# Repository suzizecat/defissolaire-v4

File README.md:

# All-in-one (AIO) board for the "Défis solaires" contest of 2024.
Board files in `main/` folder.

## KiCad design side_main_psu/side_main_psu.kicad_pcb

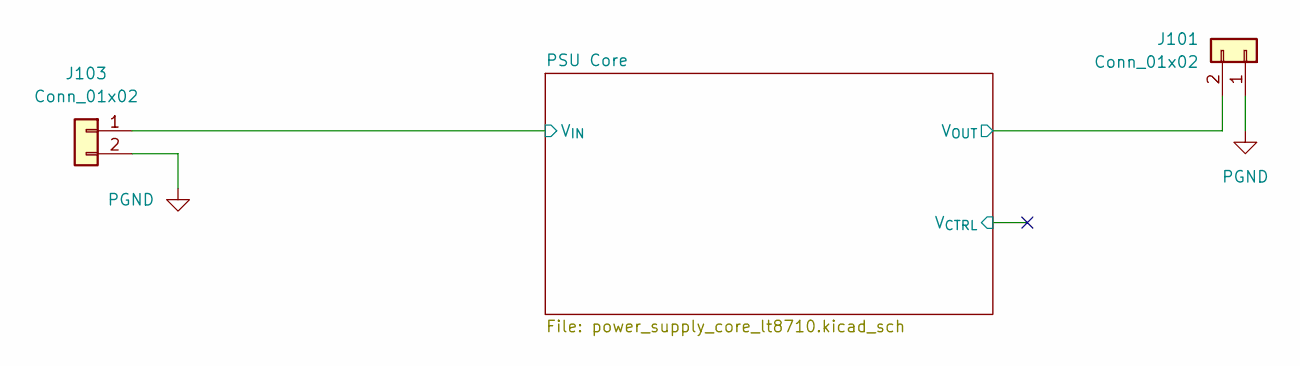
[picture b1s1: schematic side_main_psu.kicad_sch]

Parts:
J101, J103: Conn_01x02; TerminalBlock_WAGO_236-402_1x02_P5.00mm_45Degree

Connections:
/PSU Core/V_{IN}: J103.1; also elsewhere on the board
/PSU Core/V_{OUT}: J101.2; also elsewhere on the board
PGND: J101.1, J103.2; also elsewhere on the board

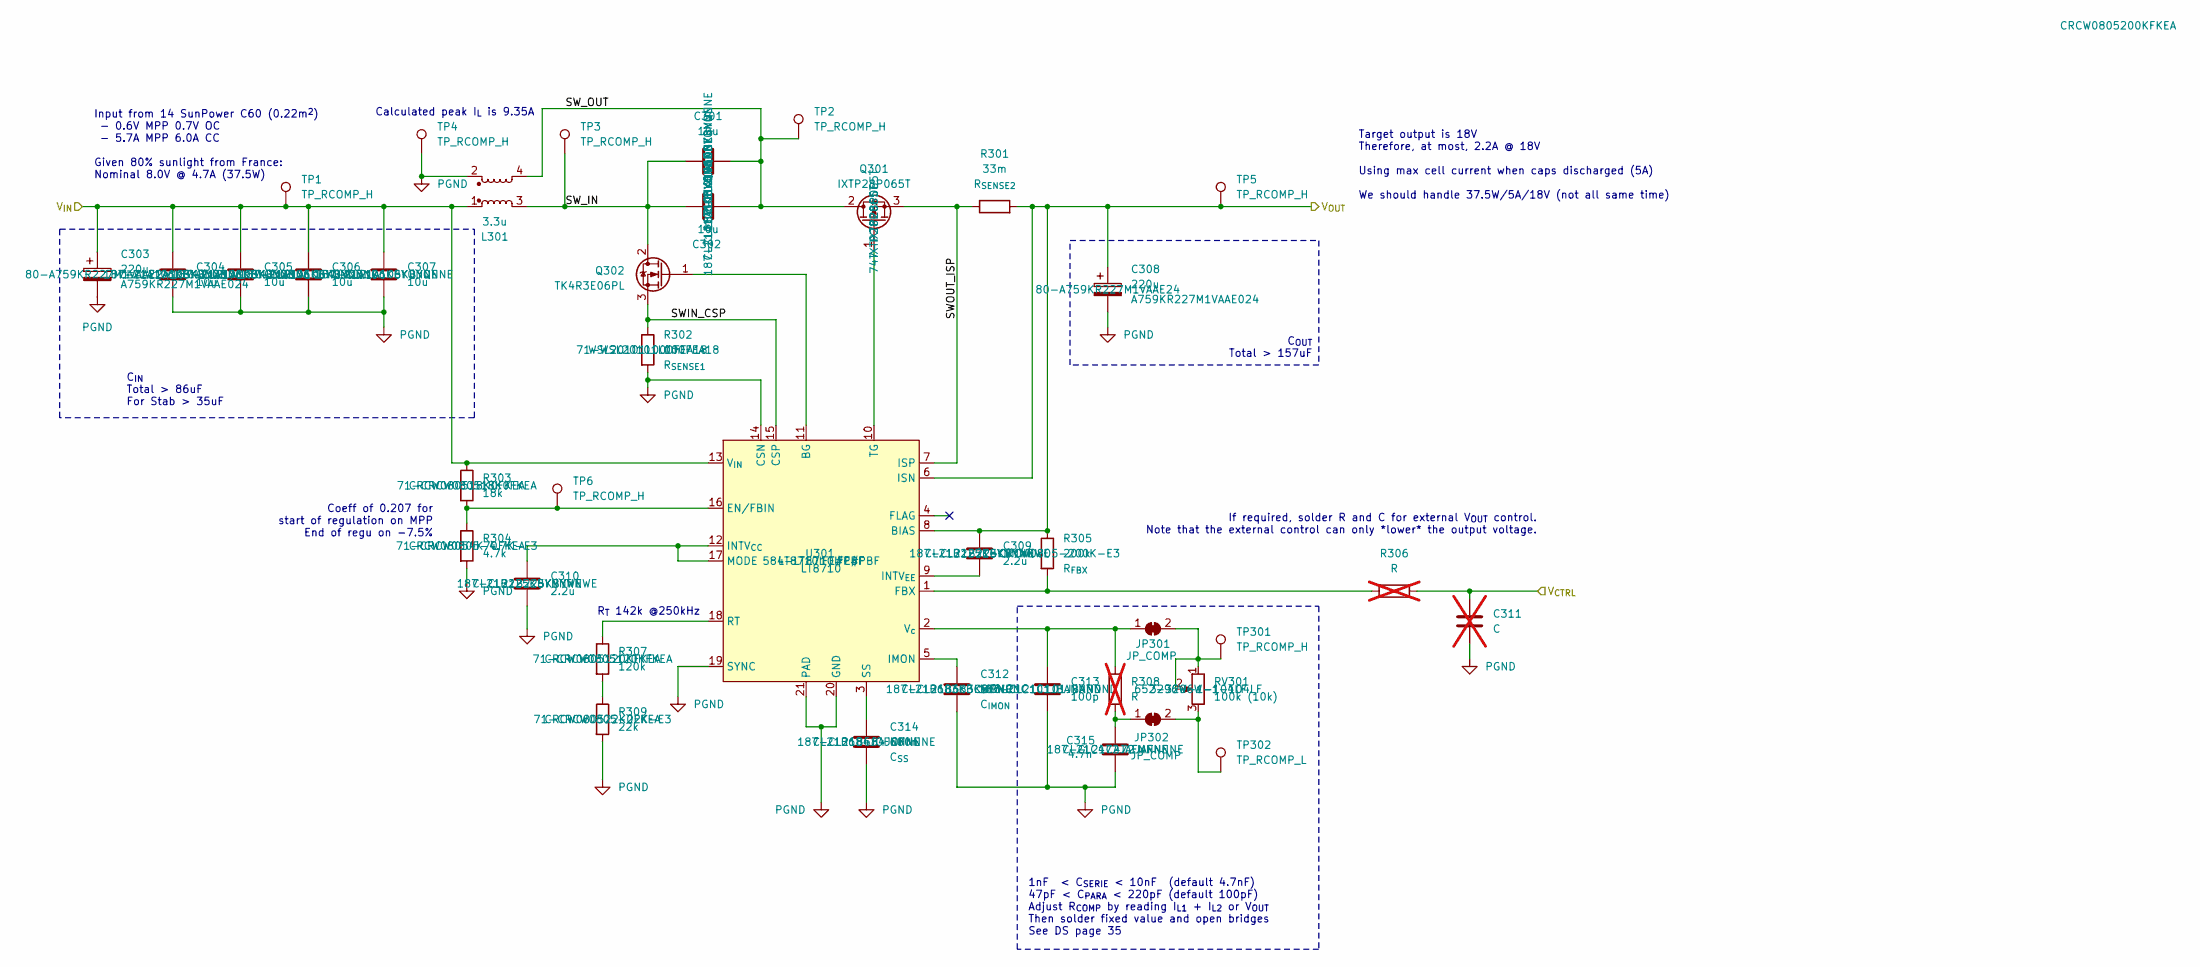
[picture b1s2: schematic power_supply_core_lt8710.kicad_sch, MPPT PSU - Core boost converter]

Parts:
C301, C302, C304, C305, C306, C307: 10u; C_0805_2012Metric; MPN CL21A106KBYQNNE; Mouser SKU 187-CL21A106KBYQNNE
C303, C308: 220u; CP_Radial_D8.0mm_P3.50mm; MPN A759KR227M1VAAE024; Mouser SKU 80-A759KR227M1VAAE24
C309, C310: 2.2u; C_0805_2012Metric; MPN CL21B225KBYNNWE; Mouser SKU 187-CL21B225KBYNNWE
C311: C; C_0805_2012Metric; not fitted
C312: 68n; C_0805_2012Metric; MPN CL21B683KBCWPNC; Mouser SKU 187-CL21B683KBCWPNC
C313: 100p; C_0805_2012Metric; MPN CL21C101JBANNND; Mouser SKU 187-CL21C101JBANNND
C314: 680n; C_0805_2012Metric; MPN CL21B684JOFNNNE; Mouser SKU 187-CL21B684JOFNNNE
C315: 4.7n; C_0805_2012Metric; MPN CL21C472JAFNNNE; Mouser SKU 187-CL21C472JAFNNNE
JP301, JP302: JP_COMP; SolderJumper-2_P1.3mm_Open_TrianglePad1.0x1.5mm
L301: 3.3u; Coilcraft_MSD1514
Q301: IXTP28P065T; TO-220-3_Horizontal_TabUp; MPN IXTP28P065T; Mouser SKU 747-IXTP28P065T
Q302: TK4R3E06PL; TO-220-3_Horizontal_TabUp; MPN TK4R3E06PL; Mouser SKU 757-TK4R3E06PLS1X
R301: 33m; R_2010_5025Metric
R302: 1m; R_2010_5025Metric; MPN WSL20101L000FEA18; Mouser SKU 71-WSL20101L000FEA18
R303: 18k; R_0805_2012Metric; MPN CRCW080518K0FKEA; Mouser SKU 71-CRCW080518K0FKEA
R304: 4.7k; R_0805_2012Metric; MPN CRCW08054K70FKEA; Mouser SKU 71-CRCW0805-4.7K-E3
R305: 200k; R_0805_2012Metric; MPN CRCW0805200KFKEA; Mouser SKU 71-CRCW0805-200K-E3
R306, R308: R; R_0805_2012Metric; not fitted
R307: 120k; R_0805_2012Metric; MPN CRCW0805120KFKEA; Mouser SKU 71-CRCW0805120KFKEA
R309: 22k; R_0805_2012Metric; MPN CRCW080522K0FKEA; Mouser SKU 71-CRCW0805-22K-E3
RV301: 100k (10k); Potentiometer_Bourns_3296W_Vertical; MPN 3296W-1-104LF; Mouser SKU 652-3296W-1-104LF
TP1, TP2, TP3, TP4, TP5, TP6, TP301: TP_RCOMP_H; TestPoint_Keystone_5010-5014_Multipurpose
TP302: TP_RCOMP_L; TestPoint_Keystone_5010-5014_Multipurpose
U301: LT8710; HTSSOP-20-1EP_4.4x6.5mm_P0.65mm_EP2.74x3.86mm; MPN LT8710IFE#PBF; Mouser SKU 584-LT8710IFE#PBF

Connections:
/PSU Core/SWIN_CSP: Q302.3 (S), R302.1, U301.15 (CSP)
/PSU Core/SWOUT_ISP: Q301.3 (S), R301.1, U301.7 (ISP)
/PSU Core/SW_IN: C301.2, C302.2, L301.3, Q302.2 (D), TP3.1
/PSU Core/SW_OUT: C301.1, C302.1, L301.4, Q301.2 (D), TP2.1
/PSU Core/V_{CTRL}: C311.1, R306.2
/PSU Core/V_{IN}: C303.1, C304.1, C305.1, C306.1, C307.1, L301.1, R303.1, TP1.1, U301.13 (V_{IN}); also elsewhere on the board
/PSU Core/V_{OUT}: C308.1, C309.1, R301.2, R305.1, TP5.1, U301.6 (ISN), U301.8 (BIAS); also elsewhere on the board
unnamed: C313.1, JP301.1 (A), R308.1, U301.2 (V_{c})
unnamed: JP301.2 (B), RV301.1, RV301.2, TP301.1
unnamed: C315.1, JP302.1 (A), R308.2
unnamed: JP302.2 (B), RV301.3, TP302.1
unnamed: Q301.1 (G), U301.10 (TG)
unnamed: Q302.1 (G), U301.11 (BG)
unnamed: R307.2, R309.1
unnamed: R303.2, R304.1, TP6.1, U301.16 (EN/FBIN)
unnamed: R305.2, R306.1, U301.1 (FBX)
unnamed: C312.1, U301.5 (IMON)
unnamed: C310.1, U301.12 (INTV_{CC}), U301.17 (MODE)
unnamed: C309.2, U301.9 (INTV_{EE})
unnamed: R307.1, U301.18 (RT)
unnamed: C314.1, U301.3 (SS)
PGND: C303.2, C304.2, C305.2, C306.2, C307.2, C308.2, C310.2, C311.2, C312.2, C313.2, C314.2, C315.2, L301.2, R302.2, R304.2, R309.2, TP4.1, U301.14 (CSN), U301.19 (SYNC), U301.20 (GND), U301.21 (PAD); also elsewhere on the board

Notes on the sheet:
If required, solder R and C for external V_{OUT} control. Note that the external control can only *lower* the output voltage.
1nF < C_{SERIE} < 10nF (default 4.7nF) 47pF < C_{PARA} < 220pF (default 100pF) Adjust R_{COMP} by reading I_{L1} + I_{L2} or V_{OUT} Then solder fixed value and open bridges See DS page 35
C_{IN} Total > 86uF For Stab > 35uF
R_{T} 142k @250kHz
Input from 14 SunPower C60 (0.22m^{2}) - 0.6V MPP 0.7V OC - 5.7A MPP 6.0A CC Given 80% sunlight from France: Nominal 8.0V @ 4.7A (37.5W)
Calculated peak I_{L} is 9.35A
C_{OUT} Total > 157uF
Coeff of 0.207 for start of regulation on MPP End of regu on -7.5%
Target output is 18V Therefore, at most, 2.2A @ 18V Using max cell current when caps discharged (5A) We should handle 37.5W/5A/18V (not all same time)

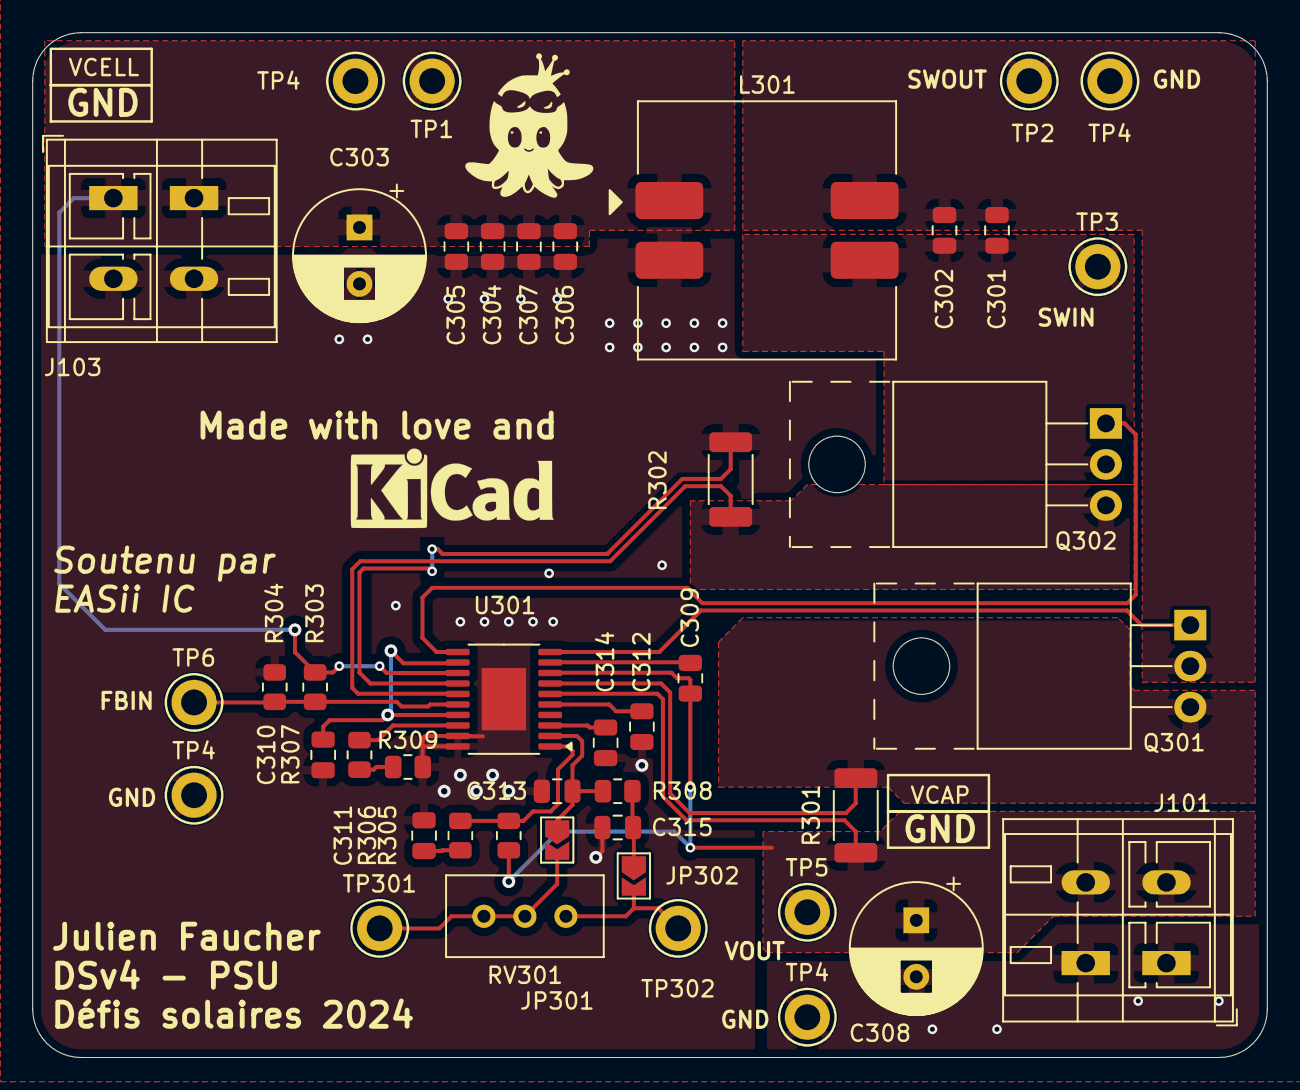
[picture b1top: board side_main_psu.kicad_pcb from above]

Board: 2 copper layers, 76.5 x 63.5 mm, 44 parts (0 on the bottom side), 22 nets.

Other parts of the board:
TP4#2, TP4#3, TP4#4: TP_GND; TestPoint_Keystone_5010-5014_Multipurpose

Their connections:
PGND: TP4#2.1, TP4#3.1, TP4#4.1; also elsewhere on the board

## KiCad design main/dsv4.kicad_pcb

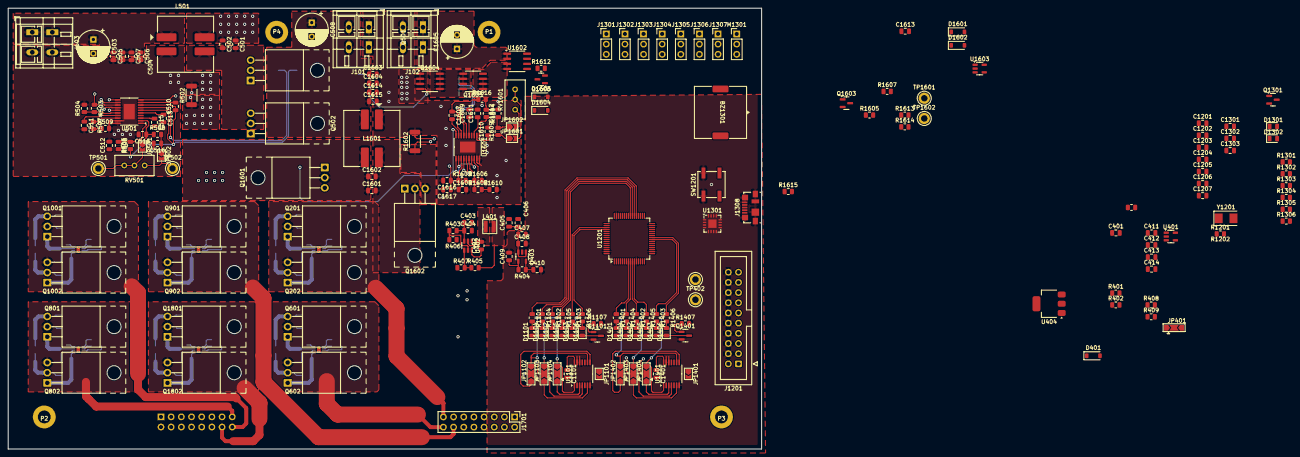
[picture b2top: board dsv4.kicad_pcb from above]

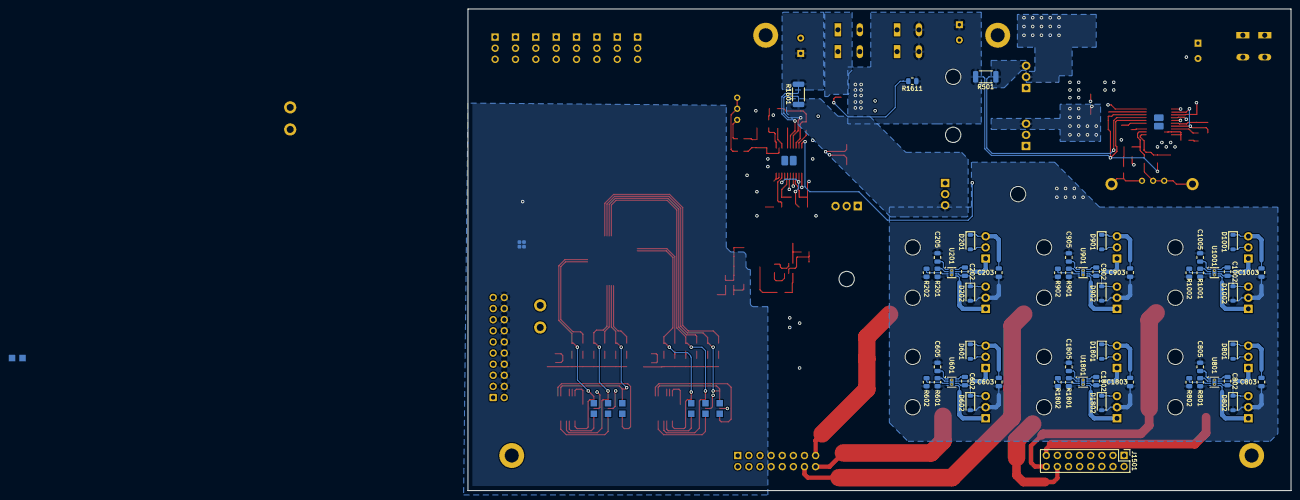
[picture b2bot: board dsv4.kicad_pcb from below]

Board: 4 copper layers, 188.0 x 110.0 mm, 261 parts (52 on the bottom side), 170 nets.

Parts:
BZ1301: PKLCS1212E4001-R1
C202, C402, C404, C408, C413, C602, C802, C902, C1002, C1101, C1201, C1202, C1203, C1204, C1205, C1303, C1401, C1617, C1802: 100n; C_0805_2012Metric
C203, C603, C803, C903, C1003, C1803: 1n; C_0805_2012Metric
C205, C407, C410, C411, C412, C414, C605, C805, C905, C1005, C1805: 1u; C_0805_2012Metric
C401, C1613: 4.7u; C_0805_2012Metric
C403, C510, C511, C1607, C1608: 2.2u; C_0805_2012Metric
C405, C406, C501, C502, C504, C505, C506, C507, C1601, C1602, C1603, C1604, C1614, C1615, C1616: 10u; C_0805_2012Metric
C409: 10n; C_0805_2012Metric
C503, C508, C1605: 220u; CP_Radial_D8.0mm_P3.50mm
C512: C; C_0805_2012Metric
C513, C1609: 62n; C_0805_2012Metric
C514, C1610: 100p; C_0805_2012Metric
C515, C1611: 560n; C_0805_2012Metric
C516, C1612: 4.7n; C_0805_2012Metric
C1206, C1207: 18p; C_0805_2012Metric
C1301, C1302: 47p; C_0805_2012Metric
D201, D202, D601, D602, D801, D802, D901, D902, D1001, D1002, D1601, D1602, D1603, D1604, D1801, D1802: B5819W-TP; D_SOD-123
D401: XBS104S14R-G; D_SOD-123
D1101, D1102, D1103, D1401, D1402, D1403: RED; LED_0805_2012Metric
D1104, D1105, D1106, D1404, D1405, D1406: BLUE; LED_0805_2012Metric
D1301, D1302: LED; LED_0805_2012Metric
J101, J102, J103: Conn_01x02; TerminalBlock_WAGO_236-402_1x02_P5.00mm_45Degree
J1201: Conn_ARM_JTAG_SWD_20; IDC-Header_2x10_P2.54mm_Vertical
J1301: Transponder; PinHeader_1x03_P2.54mm_Vertical
J1302, J1303, J1304, J1305, J1306, J1307: Conn_01x03; PinHeader_1x03_P2.54mm_Vertical
J1308: USB_B_Micro; USB_Micro-B_Molex_47346-0001
J1501, J1701: Conn_02x08_Odd_Even; PinHeader_2x08_P2.54mm_Vertical
JP401: DRIVE VSEL; SolderJumper-3_P2.0mm_Open_TrianglePad1.0x1.5mm
JP501, JP502, JP1601, JP1602: JP_COMP; SolderJumper-2_P1.3mm_Open_TrianglePad1.0x1.5mm
JP1101, JP1401: AND_PWR; SolderJumper-2_P1.3mm_Open_TrianglePad1.0x1.5mm
JP1102, JP1103, JP1104, JP1402, JP1403, JP1404: AND_BYP; SolderJumper-3_P2.0mm_Open_TrianglePad1.0x1.5mm
L401: 3.3u; VLS3015CX
L501, L1601: 3.3u; Coilcraft_MSD1260T
M1301: Servo direction; PinHeader_1x03_P2.54mm_Vertical
P1, P2, P3, P4: CONN_01X01; MountingHole_3.2mm_M3_ISO7380_Pad
Q201, Q202, Q502, Q601, Q602, Q801, Q802, Q901, Q902, Q1001, Q1002, Q1602, Q1801, Q1802: TK4R3E06PL; TO-220-3_Horizontal_TabUp
Q501, Q1601: IXTP28P065T; TO-220-3_Horizontal_TabUp
Q1101, Q1301, Q1401, Q1603, Q1606: IRLML0030; SOT-23
Q1604, Q1605: FDS6681Z; SOIC-8_3.9x4.9mm_P1.27mm
R201, R202, R601, R602, R801, R802, R901, R902, R1001, R1002, R1107, R1302, R1407, R1801, R1802: 100k; R_0805_2012Metric
R401, R406, R1613: 33k; R_0805_2012Metric
R402, R1614: 5.6k; R_0805_2012Metric
R403, R405: 150k; R_0805_2012Metric
R404: NM; R_0805_2012Metric
R407, R409: 20k; R_0805_2012Metric
R408: 2k; R_0805_2012Metric
R501, R1601: 33m; R_2010_5025Metric
R502, R1602: 1m; R_2010_5025Metric
R503, R1603: 18k; R_0805_2012Metric
R504, R1605, R1606: 4.7k; R_0805_2012Metric
R505: 200k; R_0805_2012Metric
R506, R508, R1609: R; R_0805_2012Metric
R507, R1608: 120k; R_0805_2012Metric
R509, R1610: 22k; R_0805_2012Metric
R1101, R1102, R1103, R1104, R1105, R1106, R1401, R1402, R1403, R1404, R1405, R1406: 3k3; R_0805_2012Metric
R1201, R1202, R1607, R1611, R1612, R1615: 10k; R_0805_2012Metric
R1301, R1305, R1306: 1k; R_0805_2012Metric
R1303, R1304: 27; R_0805_2012Metric
R1604, R1616: 68k; R_0805_2012Metric
RV501, RV1601: 100k (10k); Potentiometer_Bourns_3296W_Vertical
SW1201: B3SL-1022P; SW_SPST_B3SL-1022P
TP401, TP402: TestPoint; TestPoint_Keystone_5010-5014_Multipurpose
TP501, TP1601: TP_RCOMP_H; TestPoint_Keystone_5010-5014_Multipurpose
TP502, TP1602: TP_RCOMP_L; TestPoint_Keystone_5010-5014_Multipurpose
U201, U601, U801, U901, U1001, U1801: LM2105; WSON-8-1EP_2x2mm_P0.5mm_EP0.9x1.6mm_ThermalVias
U401, U1603: TSV911xxLx; SOT-23-5
U402: LMR51430; SOT-23-6
U403: LDK130M33R; SOT-23-5
U404: LM317_SOT-223; SOT-223-3_TabPin2
U501, U1601: LT8710; HTSSOP-20-1EP_4.4x6.5mm_P0.65mm_EP2.74x3.86mm
U1101, U1401: 74LS08; TSSOP-14_4.4x5mm_P0.65mm
U1201: STM32L476RGTx; LQFP-64_10x10mm_P0.5mm
U1301: FT230XQ; QFN-16-1EP_4x4mm_P0.65mm_EP2.1x2.1mm
U1602: TMCS1101; SOIC-8_3.9x4.9mm_P1.27mm
Y1201: 8MHz; Crystal_SMD_5032-2Pin_5.0x3.2mm

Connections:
+3.3V: C410.1, C1201.1, C1202.1, C1203.1, C1204.1, J1201.2 (VCC/NC), J1501.1, J1701.1, JP1101.2 (B), JP1401.2 (B), R404.1, R1201.1, R1615.1, TP401.1, U401.5 (V+), U403.5 (OUT), U1201.13 (VDDA), U1201.19 (VDD), U1201.32 (VDD), U1201.64 (VDD), U1602.8 (VS), U1603.5 (V+)
+5V: C405.1, C406.1, C407.1, C408.1, J1301.2, J1302.2, J1303.2, J1304.2, J1305.2, J1306.2, J1307.2, L401.2, M1301.2 (+), R405.2, TP402.1, U403.1 (IN), U403.3 (EN)
/CODA.A: J1701.2, U1201.14 (PA0)
/CODA.B: J1701.3, U1201.15 (PA1)
/CODB.A: J1501.2, U1201.22 (TIM3_CH1)
/CODB.B: J1501.3, U1201.23 (TIM3_CH2)
/CSN_1: J1701.11, U1201.3 (PC14)
/CSN_2: J1501.11, U1201.4 (PC15)
/MCU/BAT_OK: R1615.2, U1201.29 (PB10), U1601.4 (FLAG)
/MCU/BAT_USE: D1602.2 (A), Q1606.1 (G), U1201.30 (PB11)
/MCU/EN_BIP: Q1301.1 (G), R1302.1, U1201.50 (PA15)
/MCU/MEAS_IBAT: U1201.21 (ADC1_IN10), U1602.7 (VOUT)
/MCU/MEAS_VBAT: U1201.20 (ADC1_IN9), U1603.1, U1603.4 (-)
/MCU/MEAS_VCAP: U401.1, U401.4 (-), U1201.26 (ADC1_IN15)
/MCU/MOT1.AH: R901.1, R1401.1, U901.2 (INH), U1201.8 (PC0)
/MCU/MOT1.AL: JP1402.2 (C), R902.1, U901.3 (INL)
/MCU/MOT1.BH: R201.1, R1402.1, U201.2 (INH), U1201.10 (PC2)
/MCU/MOT1.BL: JP1403.2 (C), R202.1, U201.3 (INL)
/MCU/MOT1.CH: R601.1, R1403.1, U601.2 (INH), U1201.24 (PC4)
/MCU/MOT1.CL: JP1404.2 (C), R602.1, U601.3 (INL)
/MCU/MOT1_CMD.AL: JP1402.3 (B), R1404.1, U1201.9 (PC1), U1401.9
/MCU/MOT1_CMD.BL: JP1403.3 (B), R1405.1, U1201.11 (PC3), U1401.4
/MCU/MOT1_CMD.CL: JP1404.3 (B), R1406.1, U1201.25 (PC5), U1401.1
/MCU/MOT1_PWM: U1201.35 (TIM15_CH1), U1401.2, U1401.5, U1401.10
/MCU/MOT2.AH: R1101.1, R1801.1, U1201.37 (PC6), U1801.2 (INH)
/MCU/MOT2.AL: JP1102.2 (C), R1802.1, U1801.3 (INL)
/MCU/MOT2.BH: R801.1, R1102.1, U801.2 (INH), U1201.39 (PC8)
/MCU/MOT2.BL: JP1103.2 (C), R802.1, U801.3 (INL)
/MCU/MOT2.CH: R1001.1, R1103.1, U1001.2 (INH), U1201.51 (PC10)
/MCU/MOT2.CL: JP1104.2 (C), R1002.1, U1001.3 (INL)
/MCU/MOT2_CMD.AL: JP1102.3 (B), R1104.1, U1101.9, U1201.38 (PC7)
/MCU/MOT2_CMD.BL: JP1103.3 (B), R1105.1, U1101.4, U1201.40 (PC9)
/MCU/MOT2_CMD.CL: JP1104.3 (B), R1106.1, U1101.1, U1201.52 (PC11)
/MCU/MOT2_PWM: U1101.2, U1101.5, U1101.10, U1201.36 (TIM15_CH2)
/MCU/MOT_LED_EN: Q1101.1 (G), Q1401.1 (G), R1107.1, R1407.1, U1201.34 (PB13)
/MCU/NRST: C1205.1, J1201.3 (~TRST), R1201.2, SW1201.2, U1201.7 (NRST)
/MCU/OSC_1: C1206.1, U1201.5 (RCC_OSC_IN), Y1201.1
/MCU/OSC_2: C1207.1, U1201.6 (RCC_OSC_OUT), Y1201.2
/MCU/RADIO1: J1302.1, U1201.41 (PA8)
/MCU/RADIO2: J1303.1, U1201.42 (PA9)
/MCU/RADIO3: J1304.1, M1301.1 (PWM), U1201.43 (PA10)
/MCU/RADIO4: J1305.1, U1201.44 (PA11)
/MCU/RADIO5: J1306.1, U1201.58 (TIM4_CH1)
/MCU/RADIO6: J1307.1, U1201.59 (TIM4_CH2)
/MCU/SWCLK: J1201.9 (TCK/SWCLK), U1201.49 (SYS_JTCK-SWCLK)
/MCU/SWDIO: J1201.7 (TMS/SWDIO), U1201.46 (SYS_JTMS-SWDIO)
/MCU/USART.RX: U1201.17 (USART2_RX), U1301.15 (TXD)
/MCU/USART.TX: U1201.16 (USART2_TX), U1301.2 (RXD)
/MCU/~BAT_CHARGE: D1601.2 (A), U1201.33 (PB12)
/MOT A Connection/MOT.A: C902.2, D901.2 (A), D902.1 (K), J1701.14, Q901.2 (D), Q902.3 (S), U901.6 (SH)
/MOT A Connection/MOT.B: C202.2, D201.2 (A), D202.1 (K), J1701.15, Q201.2 (D), Q202.3 (S), U201.6 (SH)
/MOT A Connection/MOT.C: C602.2, D601.2 (A), D602.1 (K), J1701.16, Q601.2 (D), Q602.3 (S), U601.6 (SH)
/MOT B Connection/MOT.A: C1802.2, D1801.2 (A), D1802.1 (K), J1501.14, Q1801.2 (D), Q1802.3 (S), U1801.6 (SH)
/MOT B Connection/MOT.B: C802.2, D801.2 (A), D802.1 (K), J1501.15, Q801.2 (D), Q802.3 (S), U801.6 (SH)
/MOT B Connection/MOT.C: C1002.2, D1001.2 (A), D1002.1 (K), J1501.16, Q1001.2 (D), Q1002.3 (S), U1001.6 (SH)
/PSU/5VSW: C402.2, L401.1, U402.2 (SW)
/PSU/Battery chagrer/BATT_RET_PATH: Q1605.1 (S), Q1605.2 (S), Q1605.3 (S), R1612.1, U1602.3 (OUT), U1602.4 (OUT)
/PSU/Battery chagrer/BAT_RET_MID: Q1604.5 (D), Q1604.6 (D), Q1604.7 (D), Q1604.8 (D), Q1605.5 (D), Q1605.6 (D), Q1605.7 (D), Q1605.8 (D)
/PSU/Battery chagrer/SWIN_CSP: Q1602.3 (S), R1602.1, U1601.15 (CSP)
/PSU/Battery chagrer/SWOUT_ISP: Q1601.3 (S), R1601.1, U1601.7 (ISP)
/PSU/Battery chagrer/SW_IN: C1601.2, C1602.2, L1601.4, Q1602.2 (D)
/PSU/Battery chagrer/SW_OUT: C1601.1, C1602.1, L1601.3, Q1601.2 (D)
/PSU/Input PSU/SWIN_CSP: Q502.3 (S), R502.1, U501.15 (CSP)
/PSU/Input PSU/SWOUT_ISP: Q501.3 (S), R501.1, U501.7 (ISP)
/PSU/Input PSU/SW_IN: C501.2, C502.2, L501.3, Q502.2 (D)
/PSU/Input PSU/SW_OUT: C501.1, C502.1, L501.4, Q501.2 (D)
/PSU/Input PSU/V_{CTRL}: C512.1, R506.2
/PSU/V_{CELL}: C503.1, C504.1, C505.1, C506.1, C507.1, J103.1, L501.1, R503.1, U501.13 (V_{IN})
/Radio and misc/V_{FTDI}: C1303.1, D1301.2 (A), D1302.2 (A), U1301.1 (VCCIO), U1301.8 (3V3OUT), U1301.9 (~RESET)
/SPI.CLK: J1501.10, J1701.10, U1201.55 (SPI1_SCK)
/SPI.MISO: J1501.8, J1701.8, U1201.56 (SPI1_MISO)
/SPI.MOSI: J1501.9, J1701.9, U1201.57 (SPI1_MOSI)
GNDD: C203.2, C205.2, C401.2, C403.2, C404.2, C405.2, C406.2, C407.2, C408.2, C409.2, C410.2, C411.2, C412.2, C413.2, C414.2, C503.2, C504.2, C505.2, C506.2, C507.2, C508.2, C511.2, C512.2, C513.2, C514.2, C515.2, C516.2, C603.2, C605.2, C803.2, C805.2, C903.2, C905.2, C1003.2, C1005.2, C1101.2, C1201.2, C1202.2, C1203.2, C1204.2, C1205.2, C1206.2, C1207.2, C1301.2, C1302.2, C1303.2, C1401.2, C1603.2, C1604.2, C1605.2, C1608.2, C1609.2, C1610.2, C1611.2, C1612.2, C1613.2, C1614.2, C1615.2, C1616.2, C1617.2, C1803.2, C1805.2, D202.2 (A), D602.2 (A), D802.2 (A), D902.2 (A), D1002.2 (A), D1802.2 (A), J101.1, J102.2, J103.2, J1201.4 (GND), J1201.6 (GND), J1201.8 (GND), J1201.10 (GND), J1201.12 (GND), J1201.14 (GND), J1201.16 (GND), J1201.18 (GND), J1201.20 (GND), J1301.3, J1302.3, J1303.3, J1304.3, J1305.3, J1306.3, J1307.3, J1308.5 (GND), J1308.6 (Shield), J1501.12, J1501.13, J1701.12, J1701.13, L501.2, L1601.1, M1301.3 (-), Q202.2 (D), Q602.2 (D), Q802.2 (D), Q902.2 (D), Q1002.2 (D), Q1101.2 (S), Q1301.2 (S), Q1401.2 (S), Q1603.2 (S), Q1606.2 (S), Q1802.2 (D), R201.2, R202.2, R402.2, R406.1, R407.1, R409.2, R502.2, R504.2, R509.2, R601.2, R602.2, R801.2, R802.2, R901.2, R902.2, R1001.2, R1002.2, R1107.2, R1202.1, R1302.2, R1407.2, R1602.2, R1606.2, R1607.2, R1610.2, R1614.2, R1801.2, R1802.2, SW1201.1, U201.4 (GND), U201.9 (GND), U401.2 (V-), U402.1 (GND), U403.2 (GND), U501.14 (CSN), U501.19 (SYNC), U501.20 (GND), U501.21 (PAD), U601.4 (GND), U601.9 (GND), U801.4 (GND), U801.9 (GND), U901.4 (GND), U901.9 (GND), U1001.4 (GND), U1001.9 (GND), U1101.7 (GND), U1101.12, U1101.13, U1201.12 (VSSA), U1201.18 (VSS), U1201.31 (VSS), U1201.47 (VSS), U1201.63 (VSS), U1301.3 (GND), U1301.13 (GND), U1301.17 (GND), U1401.7 (GND), U1401.12, U1401.13, U1601.14 (CSN), U1601.19 (SYNC), U1601.20 (GND), U1601.21 (PAD), U1602.5 (GND), U1602.6 (NC), U1603.2 (V-), U1801.4 (GND), U1801.9 (GND)
IN: C1605.1, C1607.1, J102.1, R1601.2, R1613.1, R1616.1, U1601.6 (ISN), U1601.8 (BIAS), U1602.1 (IN), U1602.2 (IN)
unnamed: BZ1301.2 (-), Q1301.3 (D), R1301.2
unnamed: C414.1, D401.2 (A), R408.2, R409.1, U404.1 (ADJ)
unnamed: C411.1, D401.1 (K), JP401.3 (B), R408.1, U404.2 (VO)
unnamed: D1101.2 (A), R1101.2
unnamed: D1101.1 (K), D1102.1 (K), D1103.1 (K), D1104.1 (K), D1105.1 (K), D1106.1 (K), Q1101.3 (D)
unnamed: D1102.2 (A), R1102.2
unnamed: D1103.2 (A), R1103.2
unnamed: D1104.2 (A), R1104.2
unnamed: D1105.2 (A), R1105.2
unnamed: D1106.2 (A), R1106.2
unnamed: D1301.1 (K), R1305.1
unnamed: D1302.1 (K), R1306.1
unnamed: D1401.2 (A), R1401.2
unnamed: D1401.1 (K), D1402.1 (K), D1403.1 (K), D1404.1 (K), D1405.1 (K), D1406.1 (K), Q1401.3 (D)
unnamed: D1402.2 (A), R1402.2
unnamed: D1403.2 (A), R1403.2
unnamed: D1404.2 (A), R1404.2
unnamed: D1405.2 (A), R1405.2
unnamed: D1406.2 (A), R1406.2
unnamed: D1601.1 (K), D1602.1 (K), R1605.1, R1607.1
unnamed: D1603.2 (A), Q1604.4 (G), R1611.2
unnamed: D1603.1 (K), D1604.1 (K), Q1606.3 (D)
unnamed: D1604.2 (A), Q1605.4 (G), R1612.2
unnamed: C1301.1, J1308.3 (D+), R1304.2
unnamed: C1302.1, J1308.2 (D-), R1303.2
unnamed: J1308.1 (VBUS), U1301.10 (VCC)
unnamed: C514.1, JP501.1 (A), R508.1, U501.2 (V_{c})
unnamed: JP501.2 (B), RV501.1, RV501.2, TP501.1
unnamed: C516.1, JP502.1 (A), R508.2
unnamed: JP502.2 (B), RV501.3, TP502.1
unnamed: C1101.1, JP1101.1 (A), U1101.14 (VCC)
unnamed: JP1102.1 (A), U1101.8
unnamed: JP1103.1 (A), U1101.6
unnamed: JP1104.1 (A), U1101.3
unnamed: C1401.1, JP1401.1 (A), U1401.14 (VCC)
unnamed: JP1402.1 (A), U1401.8
unnamed: JP1403.1 (A), U1401.6
unnamed: JP1404.1 (A), U1401.3
unnamed: C1610.1, JP1601.1 (A), R1609.1, U1601.2 (V_{c})
unnamed: JP1601.2 (B), RV1601.1, RV1601.2, TP1601.1
unnamed: C1612.1, JP1602.1 (A), R1609.2
unnamed: JP1602.2 (B), RV1601.3, TP1602.1
unnamed: Q201.1 (G), U201.7 (GH)
unnamed: Q202.1 (G), U201.5 (GL)
unnamed: Q501.1 (G), U501.10 (TG)
unnamed: Q502.1 (G), U501.11 (BG)
unnamed: Q601.1 (G), U601.7 (GH)
unnamed: Q602.1 (G), U601.5 (GL)
unnamed: Q801.1 (G), U801.7 (GH)
unnamed: Q802.1 (G), U801.5 (GL)
unnamed: Q901.1 (G), U901.7 (GH)
unnamed: Q902.1 (G), U901.5 (GL)
unnamed: Q1001.1 (G), U1001.7 (GH)
unnamed: Q1002.1 (G), U1001.5 (GL)
unnamed: Q1601.1 (G), U1601.10 (TG)
unnamed: Q1602.1 (G), U1601.11 (BG)
unnamed: Q1603.3 (D), R1603.2, R1606.1, U1601.16 (EN/FBIN)
unnamed: Q1603.1 (G), R1605.2
unnamed: Q1801.1 (G), U1801.7 (GH)
unnamed: Q1802.1 (G), U1801.5 (GL)
unnamed: R507.2, R509.1
unnamed: R1604.1, R1616.2
unnamed: R1608.2, R1610.1
unnamed: C202.1, U201.8 (BST)
unnamed: C401.1, R401.2, R402.1, U401.3 (+)
unnamed: C402.1, U402.6 (BOOT)
unnamed: R403.1, R406.2, U402.5 (EN)
unnamed: R405.1, R407.2, U402.4 (FB)
unnamed: C409.1, R404.2, U403.4 (BP)
unnamed: R503.2, R504.1, U501.16 (EN/FBIN)
unnamed: R505.2, R506.1, U501.1 (FBX)
unnamed: C513.1, U501.5 (IMON)
unnamed: C511.1, U501.12 (INTV_{CC}), U501.17 (MODE)
unnamed: C510.2, U501.9 (INTV_{EE})
unnamed: R507.1, U501.18 (RT)
unnamed: C515.1, U501.3 (SS)
unnamed: C602.1, U601.8 (BST)
unnamed: C802.1, U801.8 (BST)
unnamed: C902.1, U901.8 (BST)
unnamed: C1002.1, U1001.8 (BST)
unnamed: R1202.2, U1201.60 (BOOT0)
unnamed: R1305.2, U1301.11 (CBUS1)
unnamed: R1306.2, U1301.5 (CBUS2)
unnamed: R1303.1, U1301.7 (USBDM)
unnamed: R1304.1, U1301.6 (USBDP)
unnamed: R1604.2, U1601.1 (FBX)
unnamed: C1609.1, U1601.5 (IMON)
unnamed: C1608.1, U1601.12 (INTV_{CC}), U1601.17 (MODE)
unnamed: C1607.2, U1601.9 (INTV_{EE})
unnamed: R1608.1, U1601.18 (RT)
unnamed: C1611.1, U1601.3 (SS)
unnamed: C1613.1, R1613.2, R1614.1, U1603.3 (+)
unnamed: C1802.1, U1801.8 (BST)
PGND: P1.1, P2.1, P3.1, P4.1
VCAP: C203.1, C403.1, C404.1, C412.1, C413.1, C508.1, C510.1, C603.1, C803.1, C903.1, C1003.1, C1603.1, C1604.1, C1614.1, C1615.1, C1616.1, C1617.1, C1803.1, D201.1 (K), D601.1 (K), D801.1 (K), D901.1 (K), D1001.1 (K), D1801.1 (K), J101.2, JP401.1 (A), L1601.2, Q201.3 (S), Q601.3 (S), Q801.3 (S), Q901.3 (S), Q1001.3 (S), Q1604.1 (S), Q1604.2 (S), Q1604.3 (S), Q1801.3 (S), R401.1, R403.2, R501.2, R505.1, R1603.1, R1611.1, U402.3 (VIN), U404.3 (VI), U501.6 (ISN), U501.8 (BIAS), U1601.13 (V_{IN})
V_{DRIVE}: BZ1301.1 (+), C205.1, C605.1, C805.1, C905.1, C1005.1, C1805.1, JP401.2 (C), R1301.1, U201.1 (VDD), U601.1 (VDD), U801.1 (VDD), U901.1 (VDD), U1001.1 (VDD), U1801.1 (VDD)
